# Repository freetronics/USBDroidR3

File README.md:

Freetronics USBDroid R3
=======================
Copyright 2011-2012 Freetronics Pty Ltd  
Freetronics site:  www.freetronics.com  
Freetronics email: info@freetronics.com  

The USBDroid is a 100% Arduino Compatible Board, based on the existing
Uno, but with improvements and updates for ease of use, cost
and getting started. It also includes on-board USB host functionality
using a dedicated port.

Features:

 * Micro-USB connector
 * Integrated USB host functionality on a dedicated USB connector
 * Overlay guide where you need it (both top and bottom)
 * D13 pin works for everything
 * RX pin biased
 * Mounting holes, power and X3 pads
 * All connections in the same place

You can view more at our product page at:

  http://www.freetronics.com/usbdroid

The "docs" folder within this repository includes a handy copy of the
schematic in PDF format, images of the pcb, and our Getting Started
guide that ships with each board.

INSTALLATION
------------
The design is saved as an EAGLE project. EAGLE PCB design software is
available from www.cadsoftusa.com free for non-commercial use. To use
this project download it and place the directory containing these files
into the "eagle" directory on your computer. Then open EAGLE and
navigate to Projects -> eagle -> USBHost.

DISTRIBUTION
------------
The specific terms of distribution of this project are governed by the
license referenced below.

LICENSE
-------
This work is licensed under the
Creative Commons Attribution-Share Alike License.  
To view a copy of this license, visit

  http://creativecommons.org/licenses/by-sa/3.0/  
  http://creativecommons.org/licenses/by-sa/3.0/legalcode

or send a letter to

  Creative Commons  
  171 Second Street, Suite 300  
  San Francisco  
  California, 94105  
  USA

The "license" folder within this repository also contains copies of the
licences referenced above.

CREDITS
-------
The USBHost was designed by Marc Alexander (marc@freetronics.com).

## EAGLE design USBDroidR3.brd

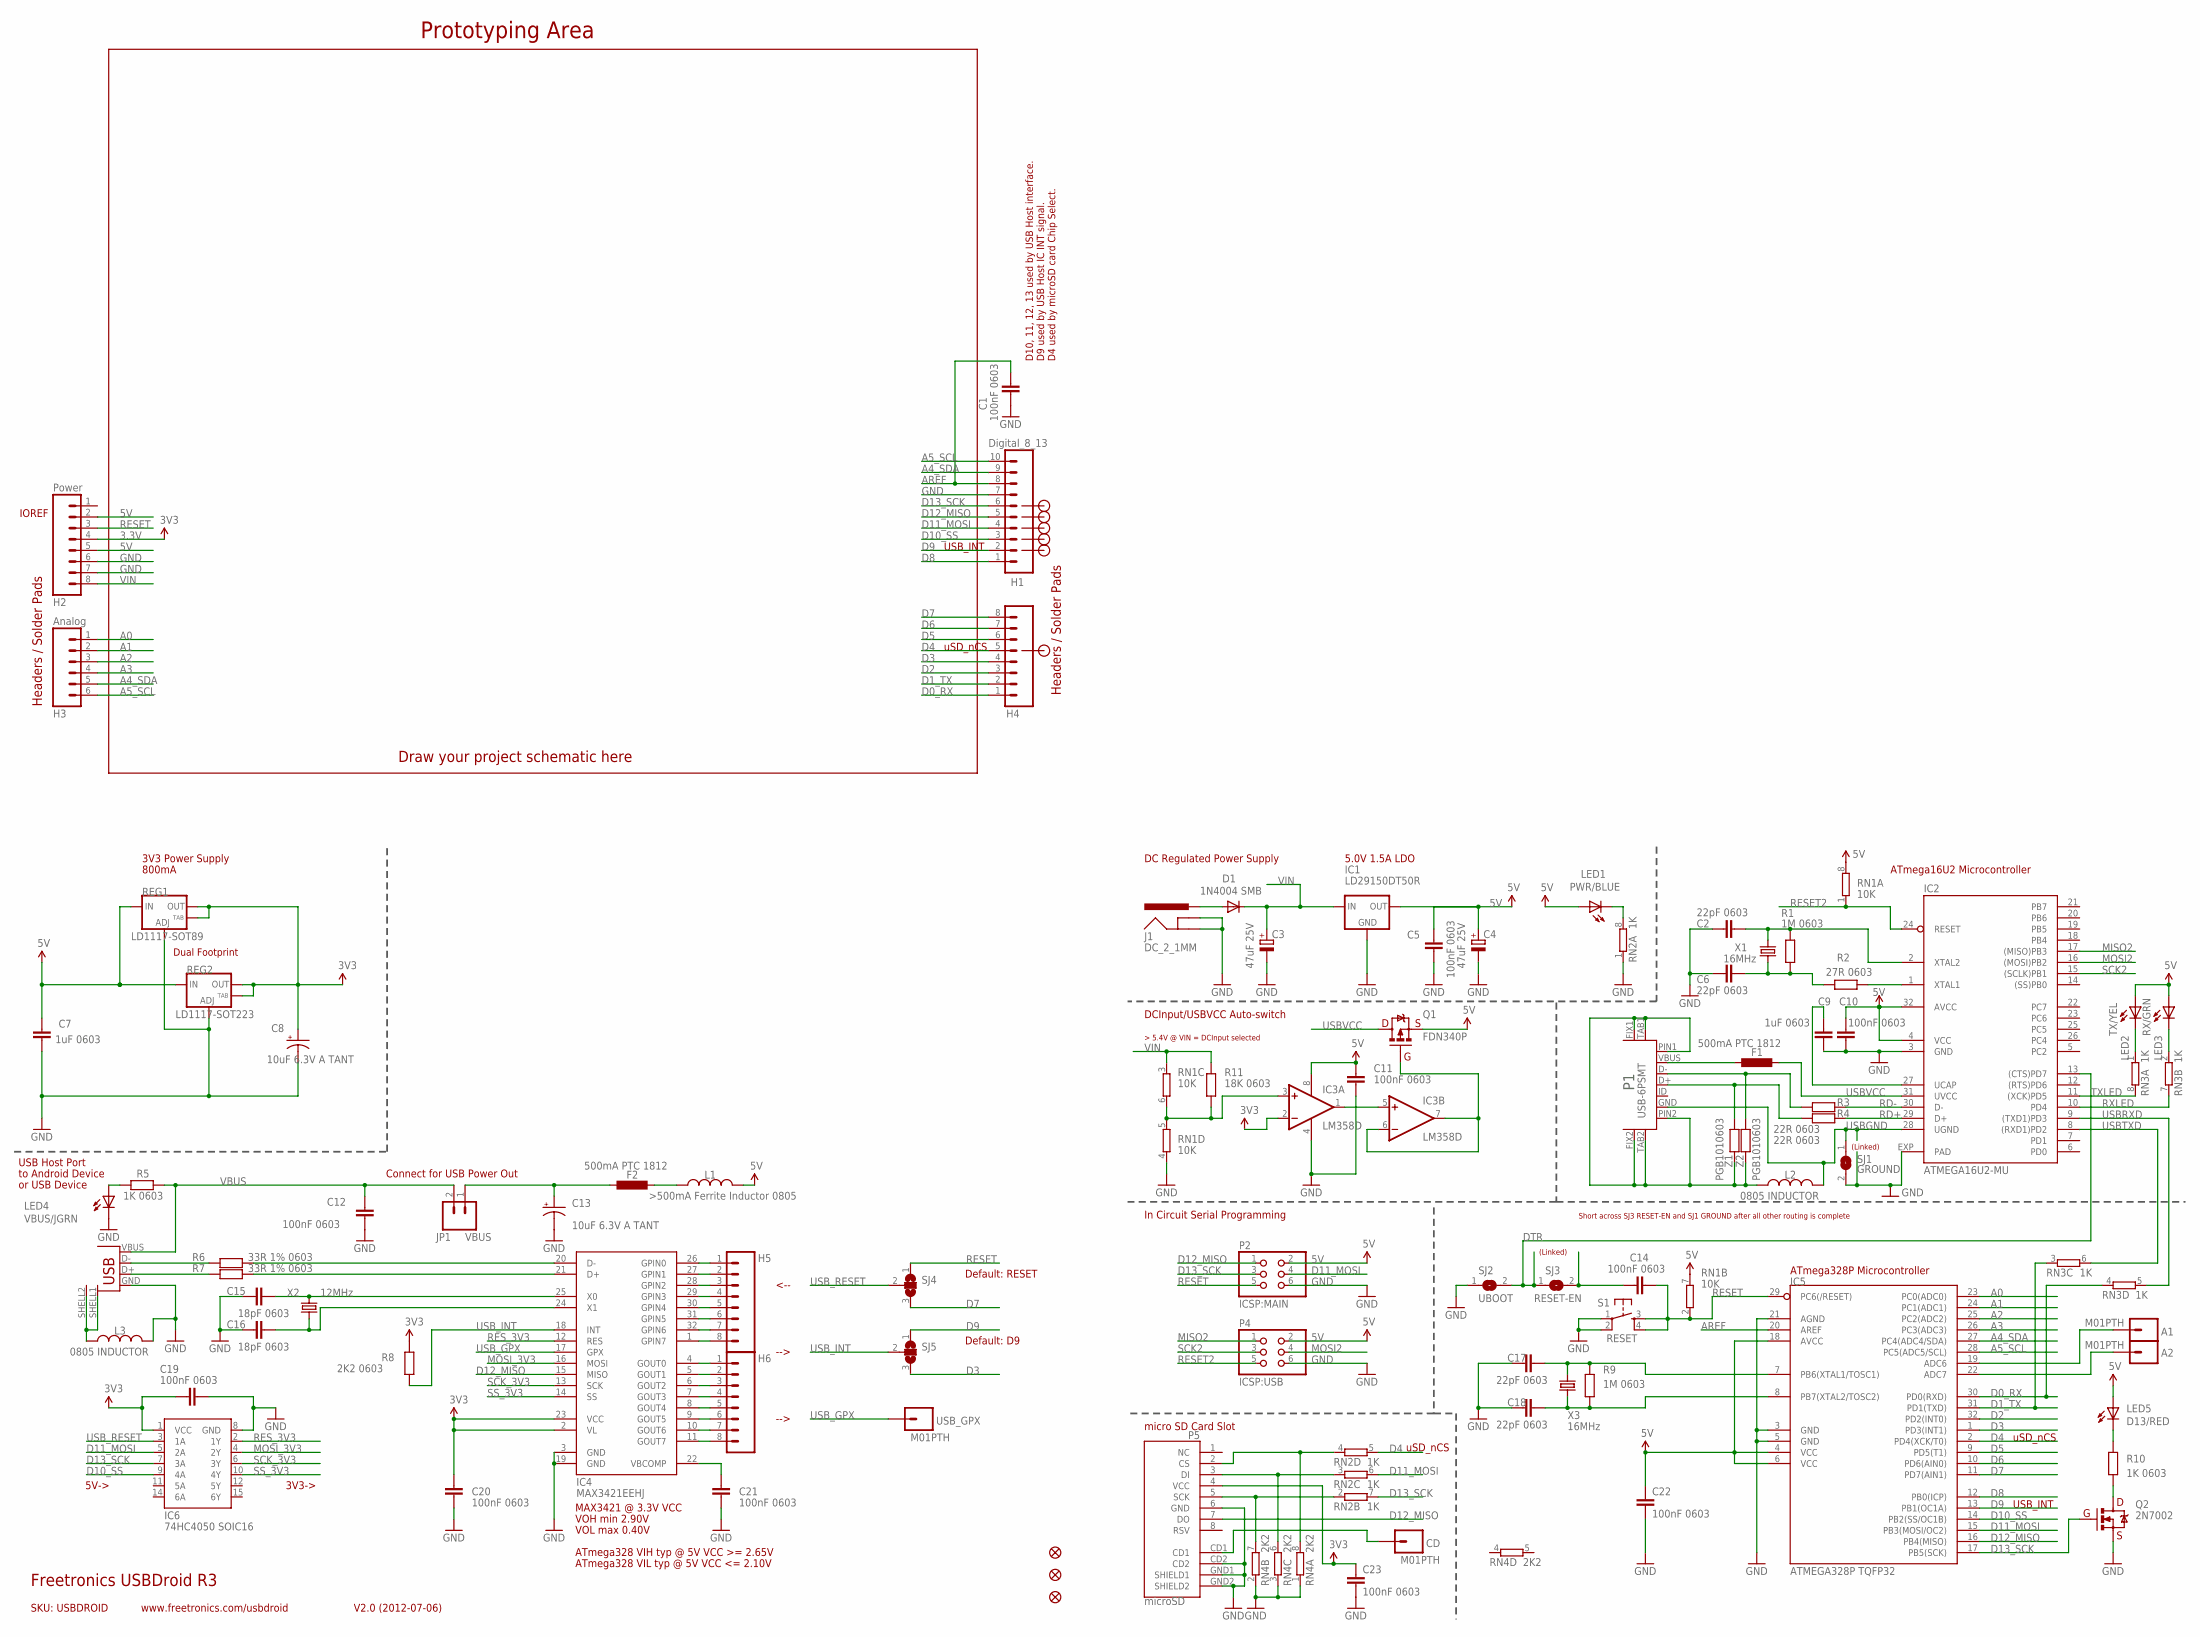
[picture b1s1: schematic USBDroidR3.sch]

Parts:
A1, A2: M01PTH; 1X01
C1, C5, C10, C11, C12, C14, C19, C20, C21, C22, C23: 100nF 0603; 0603
C2, C6, C17, C18: 22pF 0603; 0603
C3, C4: 47uF 25V; PANASONIC_D
C7, C9: 1uF 0603; 0603
C8, C13: 10uF 6.3V A TANT; EIA3216
C15, C16: 18pF 0603; 0603
CD: M01PTH; 1X01
D1: 1N4004 SMB; SMB-DIODE
F1, F2: 500mA PTC 1812; L1812
FID1, FID2, FID3: FIDUCIAL1X2.5; FIDUCIAL-1X2.5
H1: Digital_8_13; 1X10
H2: Power; 1X08
H3: Analog; 1X06
H4: Digital_0_7; 1X08
H5, H6: GPIN; 1X08
IC1: LD29150DT50R; DPACK
IC2: ATMEGA16U2-MU; ATMEL_QFN32
IC3: LM358D; SO08
IC4: MAX3421EEHJ; TQFP32-5MM
IC5: ATMEGA328P TQFP32; TQFP32-08
IC6: 74HC4050 SOIC16; SO016
J1: DC_2_1MM; POWER_JACK_PTH
JP1: VBUS; 1X02_LOCK
L1: >500mA Ferrite Inductor 0805; 0805-LARGE
L2, L3: 0805 INDUCTOR; 0805-LARGE
LED1: PWR/BLUE; LED-0603
LED2: TX/YEL; LED-0603
LED3: RX/GRN; LED-0603
LED4: VBUS/JGRN; LED-0603
LED5: D13/RED; LED-0603
P1: USB-6PSMT; USB-MICROB-MB05PMXX
P2: ICSP:MAIN; 2X03
P3: USB_; USB-A-S-SILK-FEMALE
P4: ICSP:USB; 2X03
P5: microSD; MICRO-SD-SOCKET-PP
Q1: FDN340P; SOT23
Q2: 2N7002; SOT23-3
R1, R9: 1M 0603; 0603
R2: 27R 0603; 0603
R3, R4: 22R 0603; 0603
R5, R10: 1K 0603; 0603
R6, R7: 33R 1% 0603; 0603
R8: 2K2 0603; 0603
R11: 18K 0603; 0603
REG1: LD1117-SOT89; SOT89
REG2: LD1117-SOT223; SOT223
RN1: 10K; CAY16
RN2, RN3: 1K; CAY16
RN4: 2K2; CAY16
S1: RESET; TACTILE_SWITCH_SMD
SJ1: GROUND; SJ
SJ2: UBOOT; SJ
SJ3: RESET-EN; SJ
SJ4, SJ5: SJ2W; SJ_2
USB_GPX: M01PTH; 1X01
X1, X3: 16MHz; HC49U-V
X2: 12MHz; HC49U-V
Z1, Z2: PGB1010603; 0603

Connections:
3.3V: C8.A (+), C19.2, C20.2, C23.1, H2.4, IC3.2 (-IN), IC4.2 (VL), IC4.23 (VCC), IC6.1 (VCC), P5.4 (VCC), R8.1, REG1.2 (OUT), REG1.4 (OUT), REG2.2 (OUT), REG2.4 (OUT)
5V: C4.+, C5.1, C7.1, C10.1, C11.1, C22.1, H2.2, H2.5, IC1.3 (OUT), IC2.4 (VCC), IC2.32 (AVCC), IC3.8 (V+), IC5.4 (VCC), IC5.6 (VCC), IC5.18 (AVCC), L1.2, LED1.A, LED2.A, LED3.A, LED5.A, P2.2, P4.2, Q1.2 (S), REG1.3 (IN), REG2.3 (IN), RN1.7 (2), RN1.8 (2)
A0: H3.1, IC5.23 (PC0(ADC0))
A1: H3.2, IC5.24 (PC1(ADC1))
A2: H3.3, IC5.25 (PC2(ADC2))
A3: H3.4, IC5.26 (PC3(ADC3))
A4_SDA: H1.9, H3.5, IC5.27 (PC4(ADC4/SDA))
A5_SCL: H1.10, H3.6, IC5.28 (PC5(ADC5/SCL))
AREF: C1.1, H1.8, IC5.20 (AREF)
D0_RX: H4.1, IC5.30 (PD0(RXD)), RN3.4 (1)
D1_TX: H4.2, IC5.31 (PD1(TXD)), RN3.3 (1)
D2: H4.3, IC5.32 (PD2(INT0))
D3: H4.4, IC5.1 (PD3(INT1)), SJ5.3
D4: H4.5, IC5.2 (PD4(XCK/T0)), RN2.5 (2)
D5: H4.6, IC5.9 (PD5(T1))
D6: H4.7, IC5.10 (PD6(AIN0))
D7: H4.8, IC5.11 (PD7(AIN1)), SJ4.3
D8: H1.1, IC5.12 (PB0(ICP))
D9: H1.2, IC5.13 (PB1(OC1A)), SJ5.1
D10_SS: H1.3, IC5.14 (PB2(SS/OC1B)), IC6.9 (4A)
D11_MOSI: H1.4, IC5.15 (PB3(MOSI/OC2)), IC6.5 (2A), P2.4, RN2.6 (2)
D12_MISO: H1.5, IC4.15 (MISO), IC5.16 (PB4(MISO)), P2.1, P5.7 (DO)
D13_SCK: H1.6, IC5.17 (PB5(SCK)), IC6.7 (3A), P2.3, Q2.1 (G), RN2.7 (2)
DTR: IC2.13 ((CTS)PD7), SJ2.2, SJ3.1
GND: C1.2, C2.1, C3.-, C4.-, C5.2, C6.1, C7.2, C8.C (-), C9.2, C10.2, C11.2, C12.1, C13.C (-), C15.1, C16.1, C17.1, C18.1, C19.1, C20.1, C21.1, C22.2, C23.2, H1.7, H2.6, H2.7, IC1.2 (GND), IC2.3 (GND), IC2.EXP (PAD), IC3.4 (V-), IC4.3 (GND), IC4.19 (GND), IC5.3 (GND), IC5.5 (GND), IC5.21 (AGND), IC6.8 (GND), J1.GND, J1.GNDBREAK, L3.2, LED4.C, P2.6, P3.GND, P4.6, P5.6 (GND), P5.CD2, P5.GND1 (SHIELD1), P5.GND2 (SHIELD2), Q2.2 (S), REG1.1 (ADJ), REG2.1 (ADJ), RN1.4 (1), RN2.1, RN4.1, RN4.2 (1), RN4.3 (1), S1.1, S1.2, SJ1.2, SJ2.1
MISO2: IC2.17 ((MISO)PB3), P4.1
MOSI2: IC2.16 ((MOSI)PB2), P4.4
MOSI_3V3: IC4.16 (MOSI), IC6.4 (2Y)
unnamed: P3.D-, R6.2
unnamed: C17.2, IC5.7 (PB6(XTAL1/TOSC1)), R9.2, X3.2
unnamed: P3.D+, R7.2
unnamed: LED5.C, R10.2
unnamed: IC4.20 (D-), R6.1
unnamed: Q2.3 (D), R10.1
unnamed: C18.2, IC5.8 (PB7(XTAL2/TOSC2)), R9.1, X3.1
unnamed: IC2.1 (XTAL1), R2.1
unnamed: IC4.21 (D+), R7.1
unnamed: LED3.C, RN3.2 (1)
unnamed: IC3.3 (+IN), R11.1, RN1.5 (2), RN1.6 (2)
unnamed: LED2.C, RN3.1
unnamed: LED1.C, RN2.8 (2)
unnamed: H5.1, IC4.26 (GPIN0)
unnamed: P1.D+, R4.2, Z1.1
unnamed: P1.D-, R3.2, Z2.1
unnamed: IC3.6 (-IN), IC3.7 (OUT), Q1.1 (G)
unnamed: IC3.1 (OUT), IC3.5 (+IN)
unnamed: P5.2 (CS), RN2.4 (1), RN4.8 (2)
unnamed: A2.1, IC5.22 (ADC7)
unnamed: A1.1, IC5.19 (ADC6)
unnamed: CD.1, P5.CD1
unnamed: P5.5 (SCK), RN2.2 (1), RN4.7 (2)
unnamed: P5.3 (DI), RN2.3 (1), RN4.6 (2)
unnamed: H5.2, IC4.27 (GPIN1)
unnamed: C15.2, IC4.25 (X0), X2.2
unnamed: H5.3, IC4.28 (GPIN2)
unnamed: C13.A (+), F2.1, JP1.1
unnamed: C16.2, IC4.24 (X1), X2.1
unnamed: H5.4, IC4.29 (GPIN3)
unnamed: H5.5, IC4.30 (GPIN4)
unnamed: H5.6, IC4.31 (GPIN5)
unnamed: H5.7, IC4.32 (GPIN6)
unnamed: H5.8, IC4.1 (GPIN7)
unnamed: H6.1, IC4.4 (GOUT0)
unnamed: H6.2, IC4.5 (GOUT1)
unnamed: H6.3, IC4.6 (GOUT2)
unnamed: H6.4, IC4.7 (GOUT3)
unnamed: H6.5, IC4.8 (GOUT4)
unnamed: H6.6, IC4.9 (GOUT5)
unnamed: H6.7, IC4.10 (GOUT6)
unnamed: H6.8, IC4.11 (GOUT7)
unnamed: LED4.A, R5.1
unnamed: L3.1, P3.SHELL1, P3.SHELL2
unnamed: F2.2, L1.1
unnamed: C21.2, IC4.22 (VBCOMP)
unnamed: C14.1, SJ3.2
unnamed: L2.1, P1.FIX1, P1.FIX2, P1.PIN1, P1.PIN2, P1.TAB1, P1.TAB2, Z1.2, Z2.2
unnamed: D1.A, J1.PWR
unnamed: C2.2, IC2.2 (XTAL2), R1.2, X1.2
unnamed: C6.2, R1.1, R2.2, X1.1
unnamed: F1.1, P1.VBUS
unnamed: C9.1, IC2.27 (UCAP)
RD+: IC2.29 (D+), R4.1
RD-: IC2.30 (D-), R3.1
RESET: C14.2, H2.3, IC5.29 (PC6(/RESET)), P2.5, RN1.2 (1), S1.3, S1.4, SJ4.1
RESET2: IC2.24 (RESET), P4.5, RN1.1
RES_3V3: IC4.12 (RES), IC6.2 (1Y)
RXLED: IC2.10 (PD4), RN3.7 (2)
SCK2: IC2.15 ((SCLK)PB1), P4.3
SCK_3V3: IC4.13 (SCK), IC6.6 (3Y)
SS_3V3: IC4.14 (SS), IC6.10 (4Y)
TXLED: IC2.11 ((XCK)PD5), RN3.8 (2)
USBGND: IC2.28 (UGND), L2.2, P1.GND, SJ1.1
USBRXD: IC2.9 ((TXD1)PD3), RN3.5 (2)
USBTXD: IC2.8 ((RXD1)PD2), RN3.6 (2)
USBVCC: F1.2, IC2.31 (UVCC), Q1.3 (D)
USB_GPX: IC4.17 (GPX), USB_GPX.1
USB_INT: IC4.18 (INT), R8.2, SJ5.2
USB_RESET: IC6.3 (1A), SJ4.2
VBUS: C12.2, JP1.2, P3.VBUS, R5.2
VIN: C3.+, D1.C, H2.8, IC1.1 (IN), R11.2, RN1.3 (1)

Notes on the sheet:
Prototyping Area
SKU: USBDROID
3V3 Power Supply
Headers / Solder Pads
Dual Footprint
Draw your project schematic here
D10, 11, 12, 13 used by USB Host interface.
D9 used by USB Host IC INT signal.
DC Regulated Power Supply
ATmega328P Microcontroller
ATmega16U2 Microcontroller
DCInput/USBVCC Auto-switch
uSD_nCS
800mA
In Circuit Serial Programming
micro SD Card Slot
Freetronics USBDroid R3
V2.0 (2012-07-06)
www.freetronics.com/usbdroid
D4 used by microSD card Chip Select.
5.0V 1.5A LDO
5V->
3V3->
USB Host Port
to Android Device
or USB Device
Connect for USB Power Out
VOH min 2.90V
VOL max 0.40V
ATmega328 VIH typ @ 5V VCC >= 2.65V
MAX3421 @ 3.3V VCC
ATmega328 VIL typ @ 5V VCC <= 2.10V
<--
Default: RESET
Default: D9
-->
USB_INT
IOREF
(Linked)
Short across SJ3 RESET-EN and SJ1 GROUND after all other routing is complete

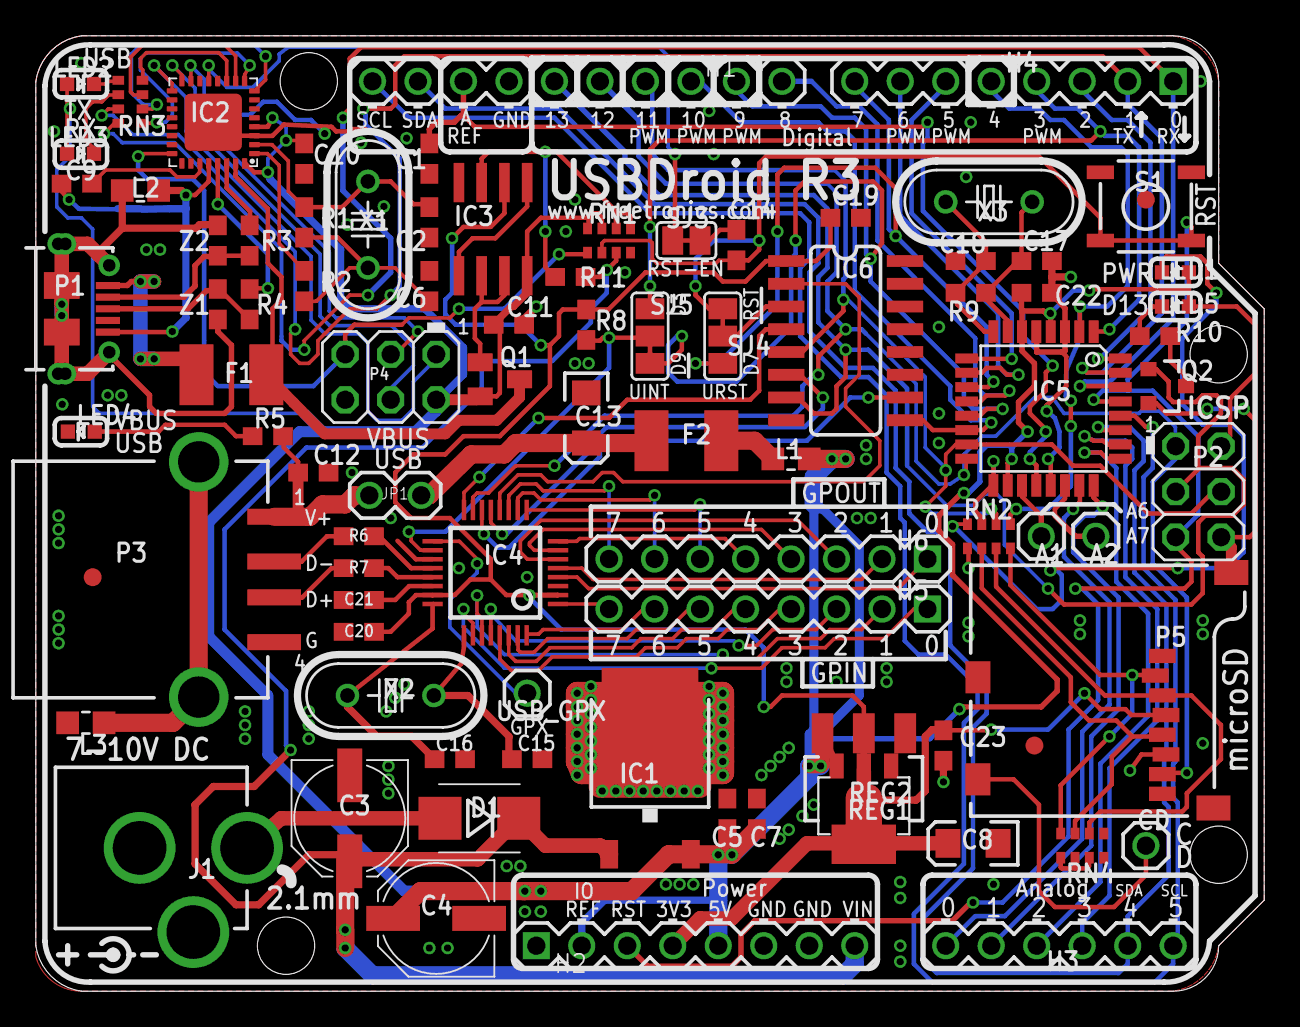
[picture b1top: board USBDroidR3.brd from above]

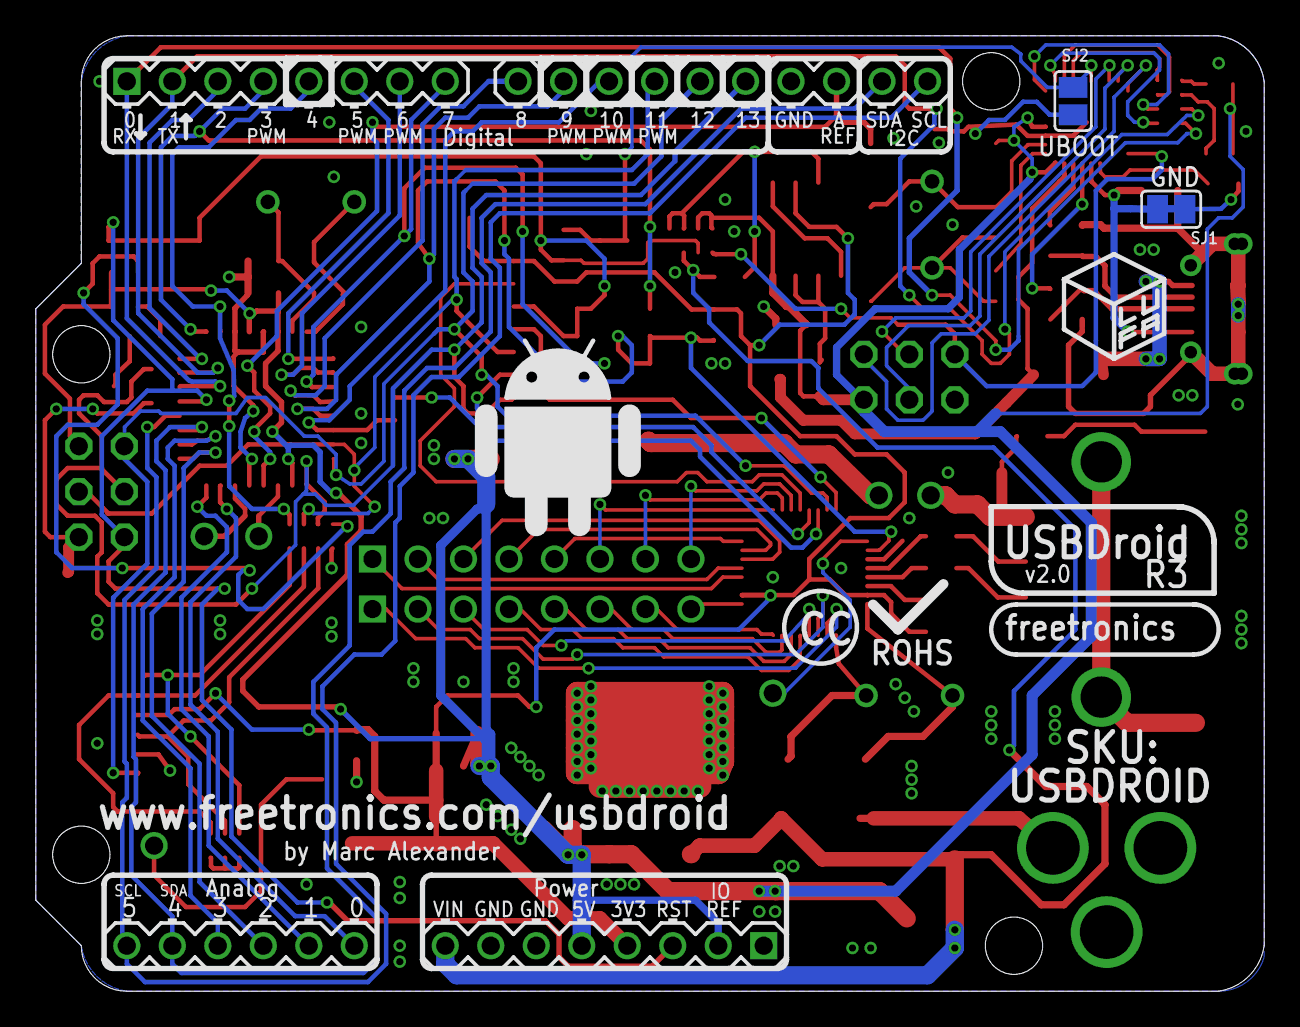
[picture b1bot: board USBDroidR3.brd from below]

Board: 2 copper layers, 68.6 x 53.3 mm, 90 parts (2 on the bottom side), 100 nets.

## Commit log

2012-07-04 Renamed project files for R3 fork
2012-07-04 Changed project name
2012-07-04 R3 headers, microUSB, 16u2
2012-07-06 R3 updates
2012-07-07 Updated designators, ERC and DRC for release
2012-07-07 R3 v2.0 production files released

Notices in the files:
parts and their libraries:
freetronics-original: Licensing: CC v3.0 Share-Alike You are welcome to use this library for commercial purposes.
